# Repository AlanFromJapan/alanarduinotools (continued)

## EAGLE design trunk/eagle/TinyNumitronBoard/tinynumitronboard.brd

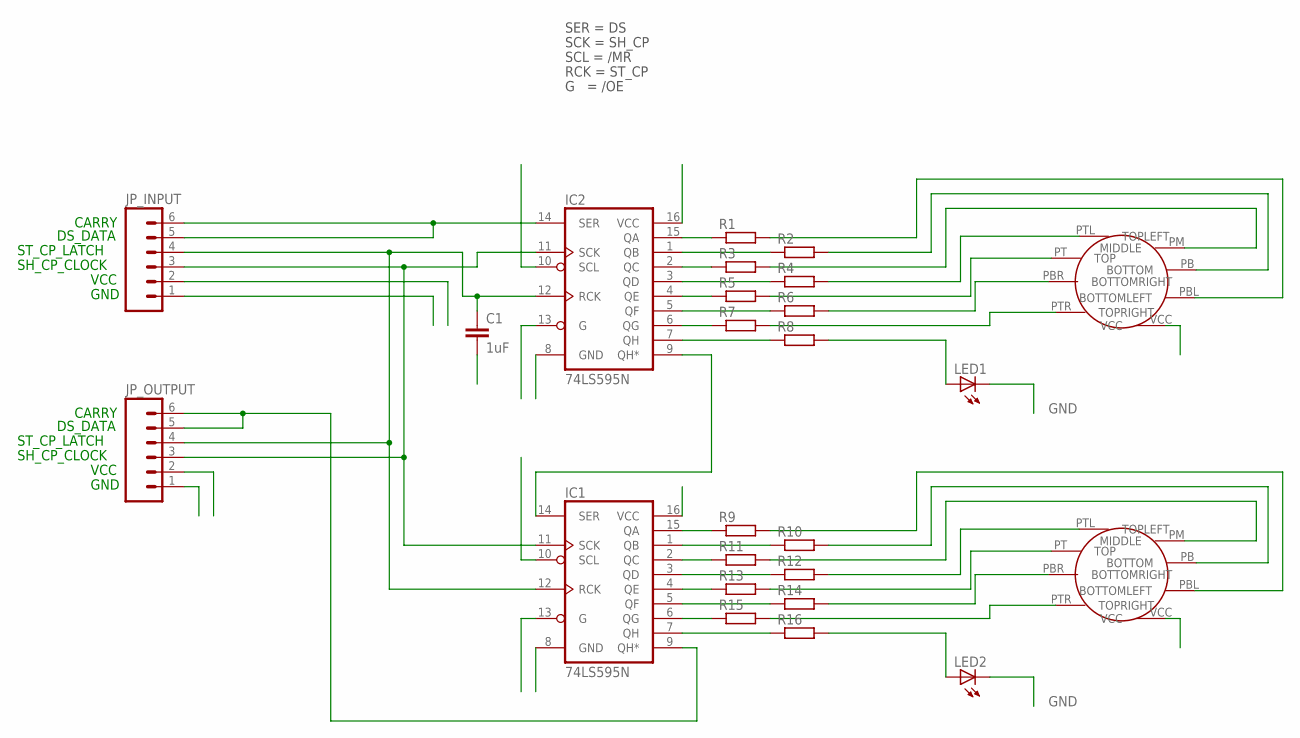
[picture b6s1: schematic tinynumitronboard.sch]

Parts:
C1: 1uF; C050-024X044
IC1, IC2: 74LS595N; DIL16
JP_INPUT: M06SIP; 1X06
JP_OUTPUT: M06SIP; 1X06
LED1, LED2: LEDKA-3528ASYC; KA-3528ASYC
R1, R2, R3, R4, R5, R6, R7, R8, R9, R10, R11, R12, R13, R14, R15, R16: R-EU_0207/10; 0207/10
U$1, U$2: IV16TINY_NUMITRON; IV16TINY_NUMITRON_PAC

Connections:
GND: C1.2, IC1.8 (GND), IC1.13 (G), IC2.8 (GND), IC2.13 (G), JP_INPUT.1, JP_OUTPUT.1, LED1.C, LED2.C
unnamed: R1.2, U$1.PBL (BOTTOMLEFT)
unnamed: R2.2, U$1.PB (BOTTOM)
unnamed: R3.2, U$1.PM (MIDDLE)
unnamed: R4.2, U$1.PTL (TOPLEFT)
unnamed: R5.2, U$1.PT (TOP)
unnamed: R6.2, U$1.PBR (BOTTOMRIGHT)
unnamed: R7.2, U$1.PTR (TOPRIGHT)
unnamed: IC2.15 (QA), R1.1
unnamed: IC2.1 (QB), R2.1
unnamed: IC2.2 (QC), R3.1
unnamed: IC2.3 (QD), R4.1
unnamed: IC2.4 (QE), R5.1
unnamed: IC2.5 (QF), R6.1
unnamed: IC2.6 (QG), R7.1
unnamed: IC2.14 (SER), JP_INPUT.5, JP_INPUT.6
unnamed: IC2.7 (QH), R8.1
unnamed: LED1.A, R8.2
unnamed: C1.1, IC1.12 (RCK), IC2.12 (RCK), JP_INPUT.4, JP_OUTPUT.4
unnamed: IC1.11 (SCK), IC2.11 (SCK), JP_INPUT.3, JP_OUTPUT.3
unnamed: R9.2, U$2.PBL (BOTTOMLEFT)
unnamed: R10.2, U$2.PB (BOTTOM)
unnamed: IC1.9 (QH*), JP_OUTPUT.5, JP_OUTPUT.6
unnamed: R11.2, U$2.PM (MIDDLE)
unnamed: R12.2, U$2.PTL (TOPLEFT)
unnamed: R13.2, U$2.PT (TOP)
unnamed: R14.2, U$2.PBR (BOTTOMRIGHT)
unnamed: R15.2, U$2.PTR (TOPRIGHT)
unnamed: IC1.15 (QA), R9.1
unnamed: IC1.1 (QB), R10.1
unnamed: IC1.2 (QC), R11.1
unnamed: IC1.3 (QD), R12.1
unnamed: IC1.4 (QE), R13.1
unnamed: IC1.5 (QF), R14.1
unnamed: IC1.6 (QG), R15.1
unnamed: IC1.7 (QH), R16.1
unnamed: LED2.A, R16.2
unnamed: IC1.14 (SER), IC2.9 (QH*)
VCC: IC1.10 (SCL), IC1.16 (VCC), IC2.10 (SCL), IC2.16 (VCC), JP_INPUT.2, JP_OUTPUT.2, U$1.VCC, U$2.VCC

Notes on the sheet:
SER = DS
SCK = SH_CP
SCL = /MR
RCK = ST_CP
G = /OE
GND
VCC
SH_CP_CLOCK
ST_CP_LATCH
DS_DATA
CARRY

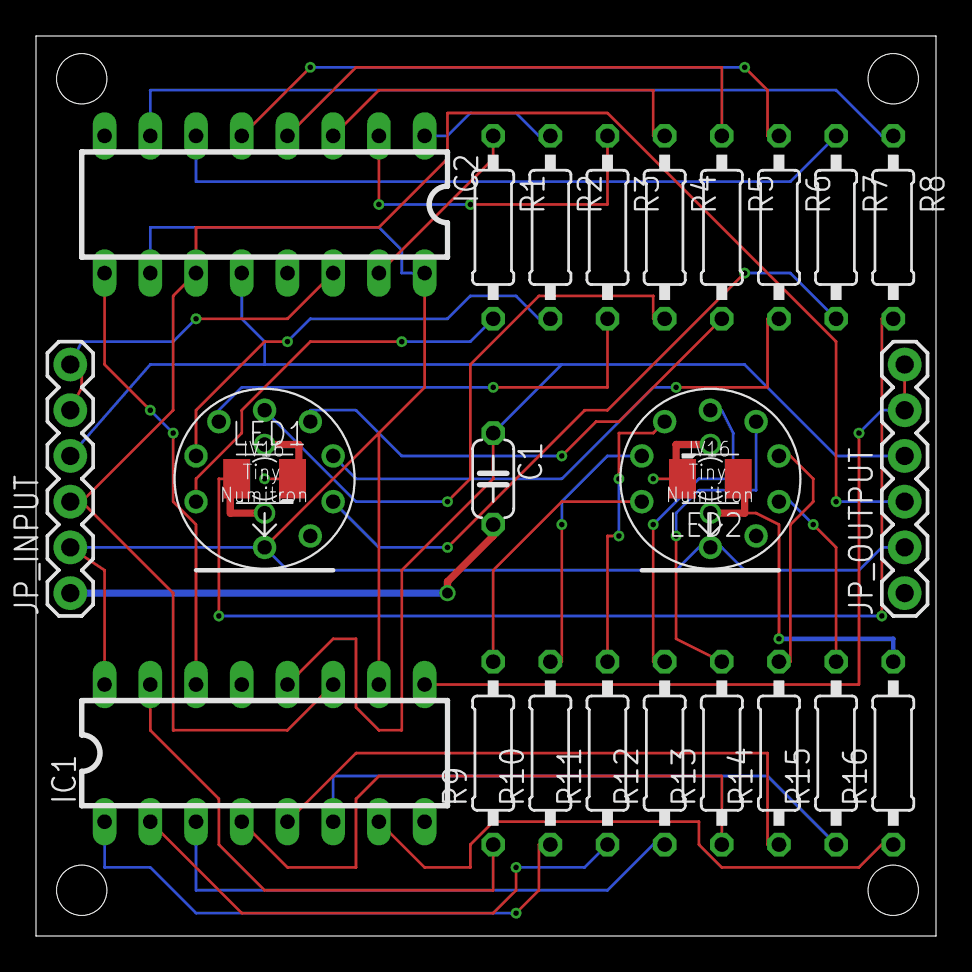
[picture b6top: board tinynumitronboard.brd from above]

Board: 2 copper layers, 50.0 x 50.0 mm, 25 parts (0 on the bottom side), 39 nets.

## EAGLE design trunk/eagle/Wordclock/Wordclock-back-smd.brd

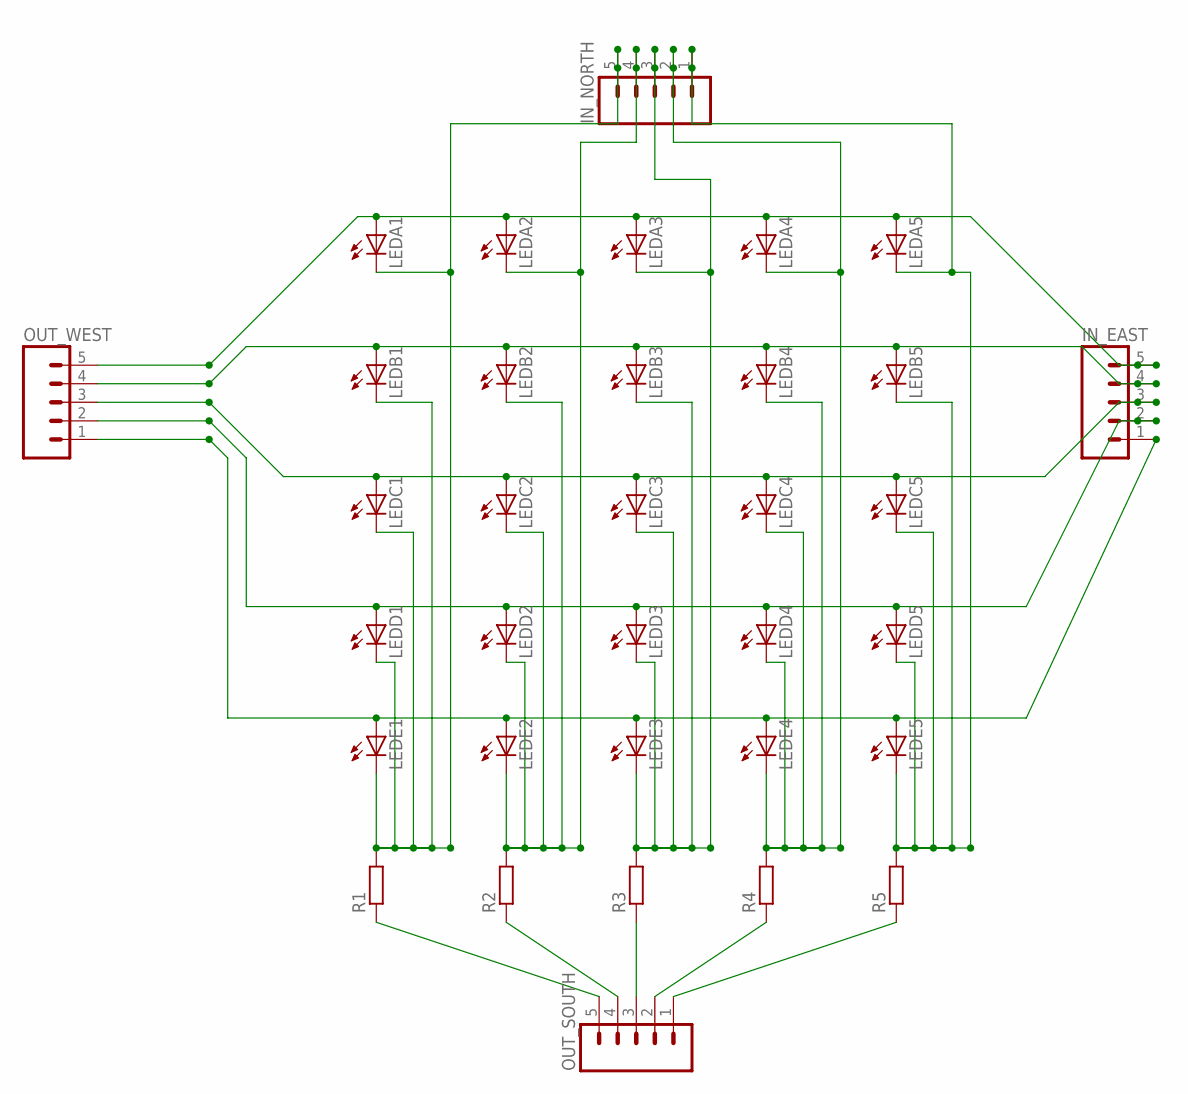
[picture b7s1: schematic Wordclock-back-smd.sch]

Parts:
IN_EAST: M05PTH; 1X05
IN_NORTH: M05PTH; 1X05
LEDA1, LEDA2, LEDA3, LEDA4, LEDA5: LEDKA-3528ASYC; KA-3528ASYC
LEDB1, LEDB2, LEDB3, LEDB4, LEDB5: LEDKA-3528ASYC; KA-3528ASYC
LEDC1, LEDC2, LEDC3, LEDC4, LEDC5: LEDKA-3528ASYC; KA-3528ASYC
LEDD1, LEDD2, LEDD3, LEDD4, LEDD5: LEDKA-3528ASYC; KA-3528ASYC
LEDE1, LEDE2, LEDE3, LEDE4, LEDE5: LEDKA-3528ASYC; KA-3528ASYC
OUT_SOUTH: M05PTH; 1X05
OUT_WEST: M05PTH; 1X05
R1, R2, R3, R4, R5: R-EU_0207/10; 0207/10

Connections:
unnamed: IN_NORTH.5, LEDA1.C, LEDB1.C, LEDC1.C, LEDD1.C, LEDE1.C, R1.2
unnamed: IN_NORTH.4, LEDA2.C, LEDB2.C, LEDC2.C, LEDD2.C, LEDE2.C, R2.2
unnamed: IN_NORTH.3, LEDA3.C, LEDB3.C, LEDC3.C, LEDD3.C, LEDE3.C, R3.2
unnamed: IN_NORTH.2, LEDA4.C, LEDB4.C, LEDC4.C, LEDD4.C, LEDE4.C, R4.2
unnamed: IN_NORTH.1, LEDA5.C, LEDB5.C, LEDC5.C, LEDD5.C, LEDE5.C, R5.2
unnamed: OUT_SOUTH.1, R5.1
unnamed: OUT_SOUTH.2, R4.1
unnamed: OUT_SOUTH.3, R3.1
unnamed: OUT_SOUTH.4, R2.1
unnamed: OUT_SOUTH.5, R1.1
unnamed: IN_EAST.5, LEDA1.A, LEDA2.A, LEDA3.A, LEDA4.A, LEDA5.A, OUT_WEST.5
unnamed: IN_EAST.4, LEDB1.A, LEDB2.A, LEDB3.A, LEDB4.A, LEDB5.A, OUT_WEST.4
unnamed: IN_EAST.3, LEDC1.A, LEDC2.A, LEDC3.A, LEDC4.A, LEDC5.A, OUT_WEST.3
unnamed: IN_EAST.2, LEDD1.A, LEDD2.A, LEDD3.A, LEDD4.A, LEDD5.A, OUT_WEST.2
unnamed: IN_EAST.1, LEDE1.A, LEDE2.A, LEDE3.A, LEDE4.A, LEDE5.A, OUT_WEST.1

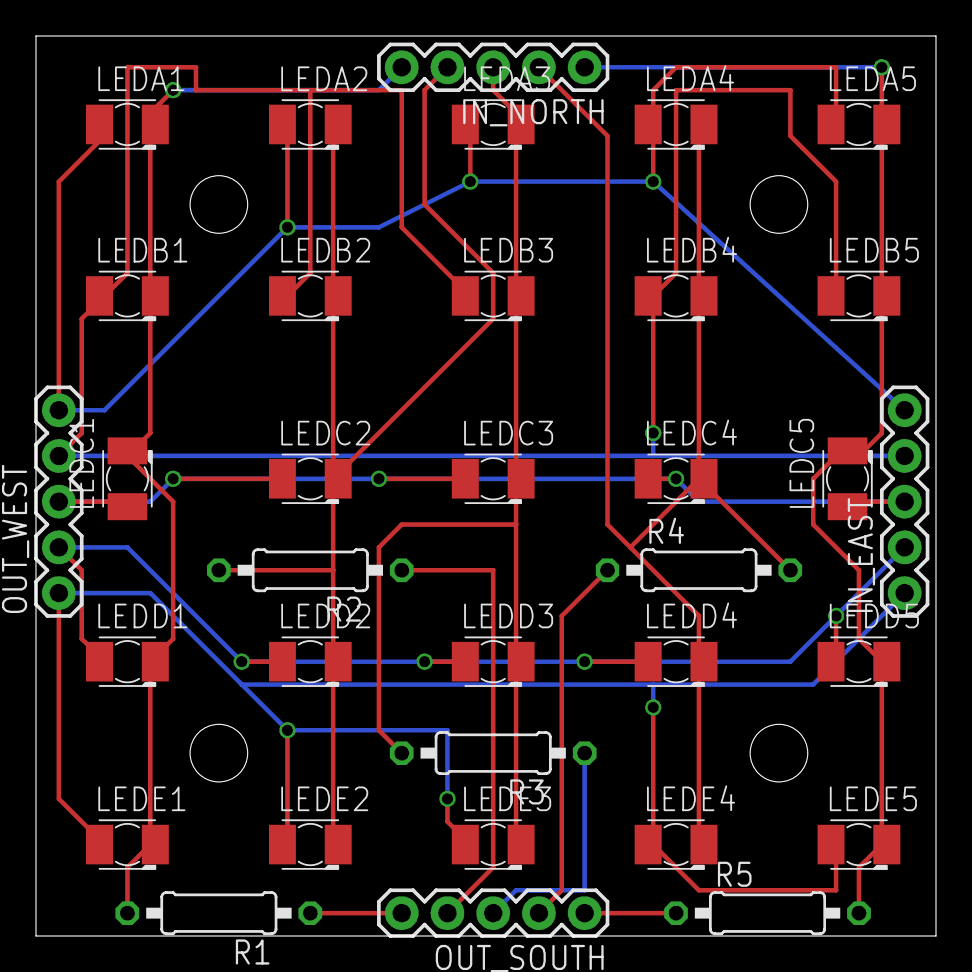
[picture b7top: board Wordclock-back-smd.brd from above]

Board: 2 copper layers, 50.0 x 50.0 mm, 34 parts (0 on the bottom side), 15 nets.
